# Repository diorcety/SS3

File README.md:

# SS3 — Solder Station 3

A DIY Weller-compatible soldering station controller, inspired by the [kair.us Weller WMRP and WMRT compatible soldering station](http://kair.us/projects/weller/index.html).

## Overview

SS3 is a two-board redesign of the kair.us open-source solder station. The key differences from the original are:

- **Transformer-based power supply** instead of SMPS — cleaner, simpler, lower EMI
- **Native 12V and 24V tip support** — handle type is identified by reading a resistor inside the handle via a voltage divider (510Ω for WXUP, 1kΩ for WMRP, 2kΩ for WMRT)
- **MSPM0G1507SRHBR MCU** (Texas Instruments) replacing the PIC16F1788
- **Dual MOSFET back-to-back switching stage** acting as a solid-state triac with minimal conduction losses

## Hardware — Two Boards

### MCU / Display Board
Handles all control logic, ADC measurements, and user interface.

- MSPM0G1507SRHBR microcontroller (default)
  - MSPM0G1505SRHBR can be used for 7-segment display builds
  - MSPM0G1506SRHBR can be used for TFT display builds
  - Switching variant requires updating `device_linker.cmd`
- Onboard ADC for thermocouple sensing (cold-junction compensation is handled inside the handle itself)
- Display support:
  - 4× 7-segment LED display
  - 1.9" TFT color screen

### Power Board
Drives the resistive heating element of the tip.

- Four dual N-MOSFET ICs (8 MOSFETs total), one per heating channel: two channels (left/right) × two voltages (12V/24V), each pair wired back-to-back
- Each pair acts as a solid-state triac equivalent, covering both 12V and 24V channels
- Lower switching losses compared to a traditional triac

## Tip Compatibility

Compatible with Weller active tips using an integrated heater and thermocouple:

- **WMRP** — soldering pen (12V)
- **WMRT** — desoldering tweezers (12V)
- **WXUP** — soldering pen (24V)

## Directory Structure

```
SS3/
├── 3D/       — Stands and handle models (12V and 24V variants; no enclosure provided)
├── PCBS/     — KiCad / Gerber files for both boards, plus KiCad conversions of the
│              original kair.us WMRP and WMRT boards (including mirrored variant for
│              mirrored jack barrels)
├── SIMS/     — LTSpice simulations: zero-cross detection, 3.6V SMPS from half-wave
│              rectifier, and back-to-back N-MOSFET triac equivalent
└── SS3/      — Firmware source (CMake project)
```

## Credits

Based on the open-source [Weller WMRP and WMRT compatible soldering station](http://kair.us/projects/weller/index.html) by kair.us.

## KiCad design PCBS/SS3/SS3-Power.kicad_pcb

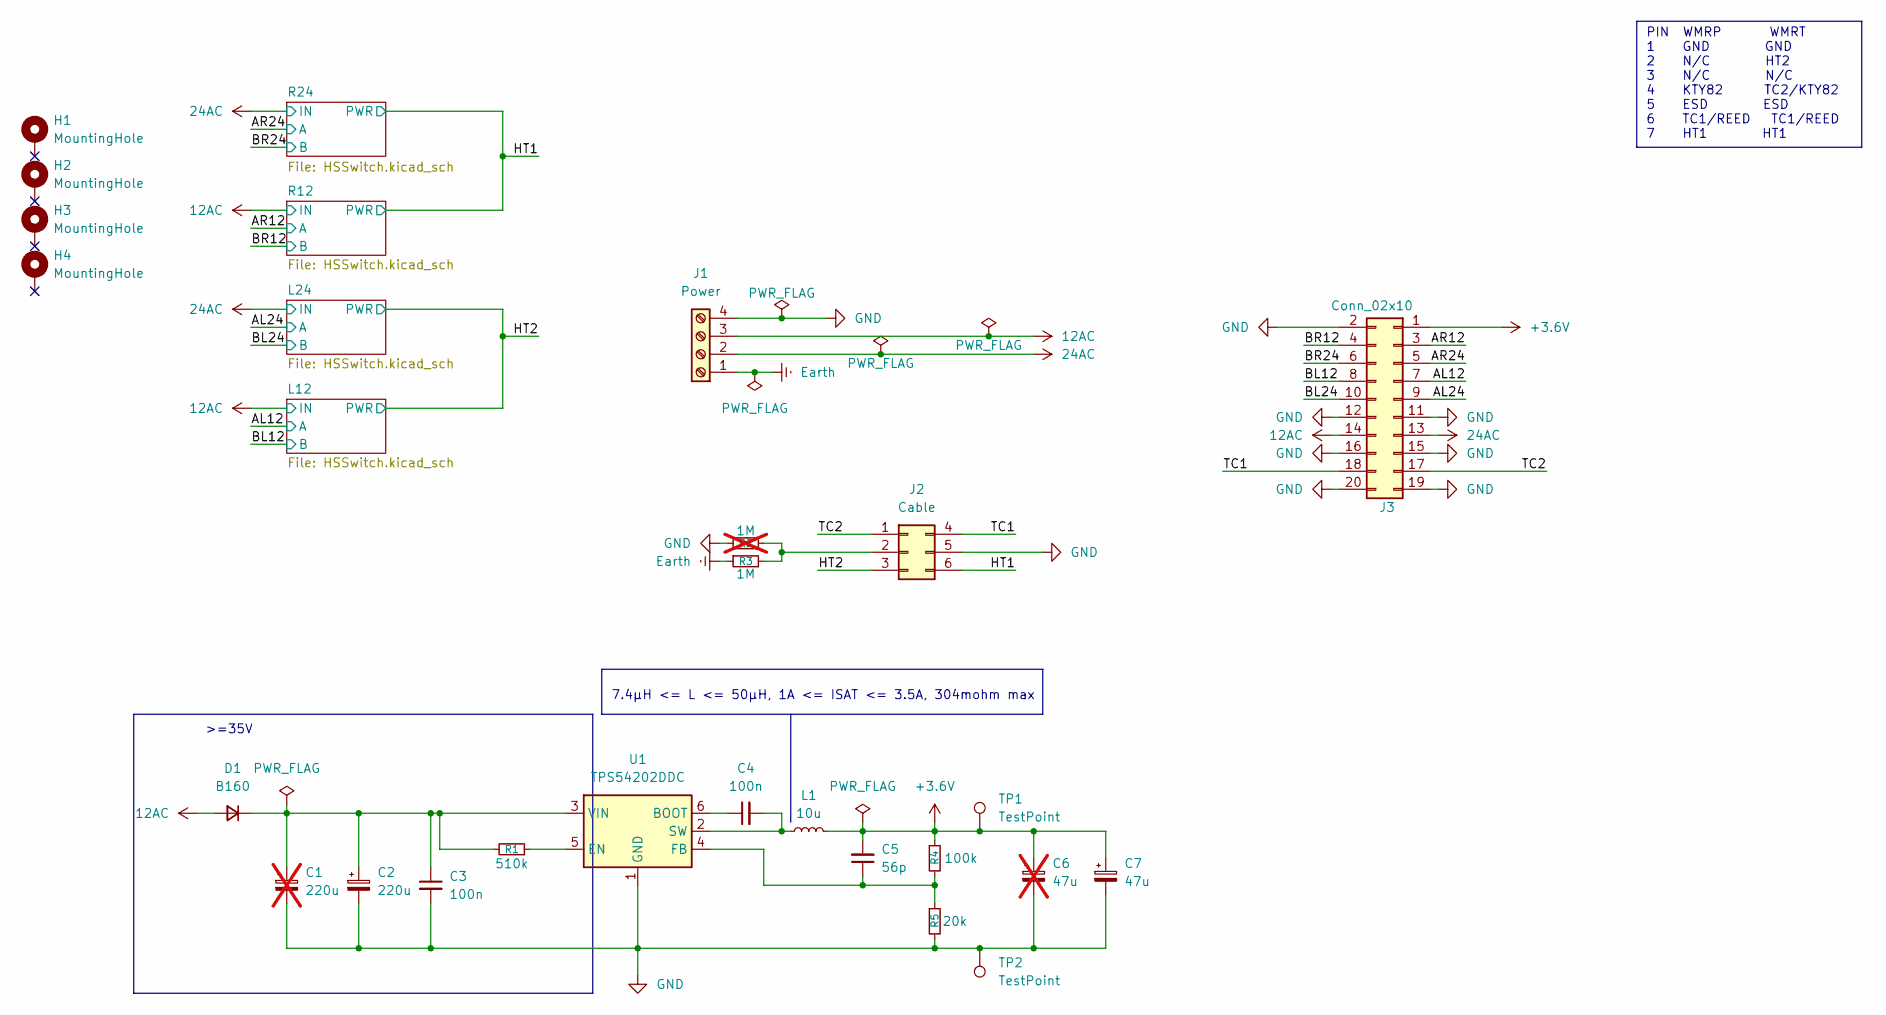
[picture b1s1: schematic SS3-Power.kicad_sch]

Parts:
C1: 220u; CP_Elec_10x10.5; not fitted
C2: 220u; CP_Elec_10x10.5
C3, C4: 100n; C_0402_1005Metric
C5: 56p; C_0402_1005Metric
C6: 47u; CP_Elec_6.3x5.9; not fitted
C7: 47u; CP_Elec_6.3x5.9
D1: B160; D_SMB
H1, H2, H3, H4: MountingHole; MountingHole_2mm_M1.8_Pad
J1: Power; TerminalBlock_Phoenix_PT-1,5-4-3.5-H_1x04_P3.50mm_Horizontal
J2: Cable; 10127720-061LF
J3: Conn_02x10; BF030-20A-B1-0360
L1: 10u; L_Chilisin_BWVS00606045
R1: 510k; R_0402_1005Metric
R2: 1M; R_0402_1005Metric; not fitted
R3: 1M; R_0402_1005Metric
R4: 100k; R_0402_1005Metric
R5: 20k; R_0402_1005Metric
TP1, TP2: TestPoint; TestPoint_THTPad_D2.0mm_Drill1.0mm
U1: TPS54202DDC; SOT-23-6

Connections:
12AC: D1.2 (A), J1.3, J3.14; also elsewhere on the board
24AC: J1.2, J3.13; also elsewhere on the board
+3.6V: C5.2, C6.1, C7.1, J3.1, L1.2, R4.1, TP1.1 (1_1)
/AL12: J3.7; also elsewhere on the board
/AL24: J3.9; also elsewhere on the board
/AR12: J3.3; also elsewhere on the board
/AR24: J3.5; also elsewhere on the board
/BL12: J3.8; also elsewhere on the board
/BL24: J3.10; also elsewhere on the board
/BR12: J3.4; also elsewhere on the board
/BR24: J3.6; also elsewhere on the board
/HT1: J2.6; also elsewhere on the board
/HT2: J2.3; also elsewhere on the board
/TC1: J2.4, J3.18
/TC2: J2.1, J3.17
Earth: J1.1, R3.1
GND: C1.2, C2.2, C3.2, C6.2, C7.2, J1.4, J2.5, J3.2, J3.11, J3.12, J3.15, J3.16, J3.19, J3.20, R2.2, R5.2, TP2.1 (1_1), U1.1 (GND); also elsewhere on the board
unnamed: C1.1, C2.1, C3.1, D1.1 (K), R1.2, U1.3 (VIN)
unnamed: J2.2, R2.1, R3.2
unnamed: C4.1, U1.6 (BOOT)
unnamed: R1.1, U1.5 (EN)
unnamed: C5.1, R4.2, R5.1, U1.4 (FB)
unnamed: C4.2, L1.1, U1.2 (SW)

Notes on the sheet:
PIN WMRP WMRT 1 GND GND 2 N/C HT2 3 N/C N/C 4 KTY82 TC2/KTY82 5 ESD ESD 6 TC1/REED TC1/REED 7 HT1 HT1
>=35V
7.4μH <= L <= 50μH, 1A <= ISAT <= 3.5A, 304mohm max

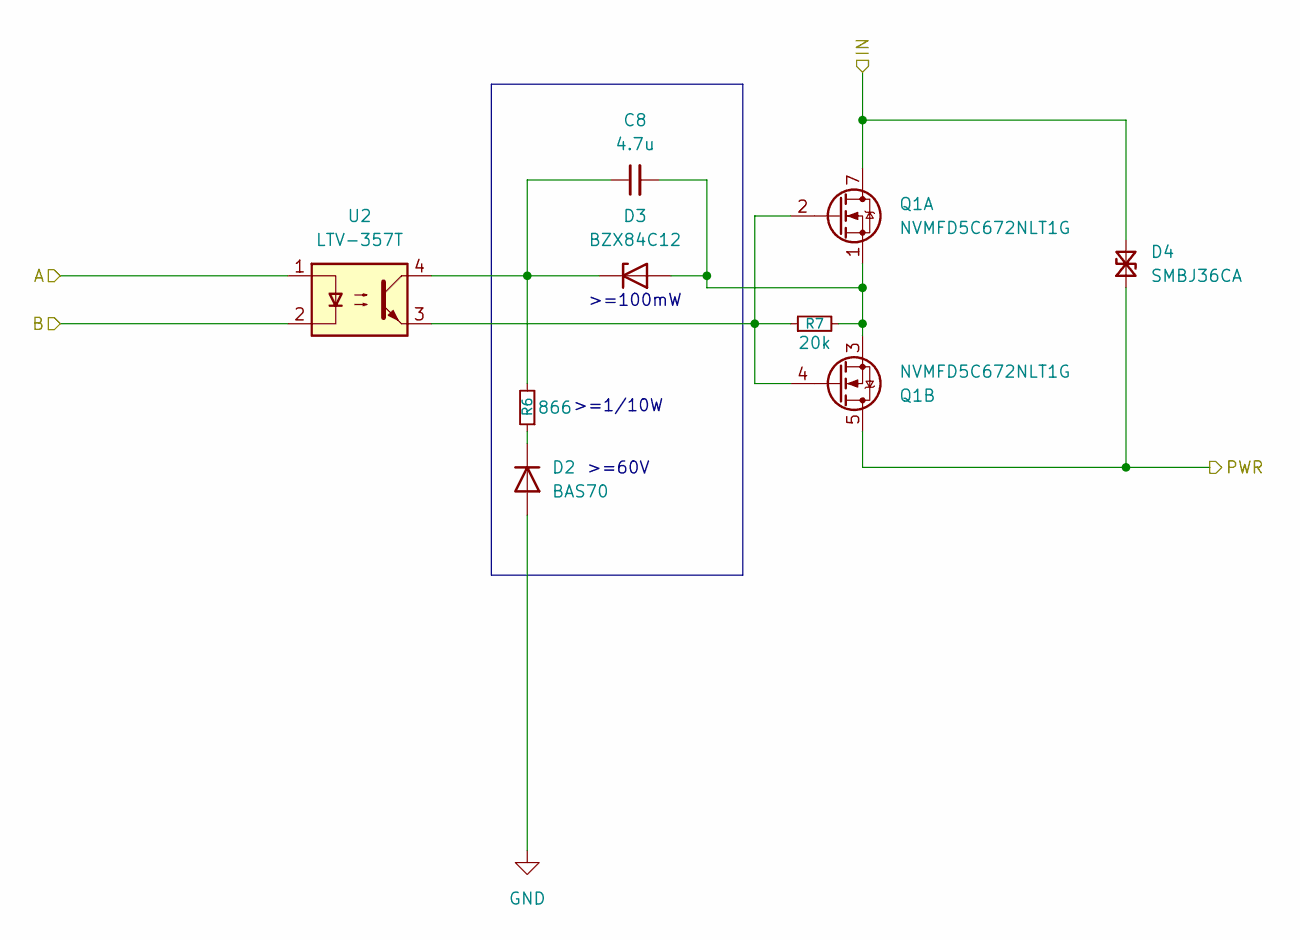
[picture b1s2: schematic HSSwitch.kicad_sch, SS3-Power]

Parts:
C8: 4.7u; C_0805_2012Metric
D2: BAS70; SOT-23
D3: BZX84C12; SOT-23
D4: SMBJ36CA; D_SMB
Q1: NVMFD5C672NLT1G; Mouser Part Number 863-NVMFD5C672NLT1G
R6: 866; R_0805_2012Metric
R7: 20k; R_0402_1005Metric
U2: LTV-357T; SO-4_4.4x3.6mm_P2.54mm

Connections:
24AC: D4.2 (A2), Q1.7, Q1.8 (D), Q1.9 (D), Q1.10 (D), Q1.11 (D); also elsewhere on the board
/AR24: U2.1; also elsewhere on the board
/BR24: U2.2; also elsewhere on the board
/HT1: D4.1 (A1), Q1.5, Q1.6 (D), Q1.12 (D), Q1.13 (D), Q1.14 (D); also elsewhere on the board
GND: D2.1 (A); also elsewhere on the board
unnamed: D2.3 (K), R6.1
unnamed: C8.2, D3.1 (A), Q1.1, Q1.3, R7.2
unnamed: C8.1, D3.3 (K), R6.2, U2.4
unnamed: Q1.2, Q1.4, R7.1, U2.3

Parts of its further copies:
C9, C10, C11: 4.7u; C_0805_2012Metric
D5, D8, D11: BAS70; SOT-23
D6, D9, D12: BZX84C12; SOT-23
D7, D10, D13: SMBJ36CA; D_SMB
Q2, Q3, Q4: NVMFD5C672NLT1G; Mouser Part Number 863-NVMFD5C672NLT1G
R8, R10, R12: 866; R_0805_2012Metric
R9, R11, R13: 20k; R_0402_1005Metric
U3, U4, U5: LTV-357T; SO-4_4.4x3.6mm_P2.54mm

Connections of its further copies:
12AC: D7.2 (A2), D13.2 (A2), Q2.7, Q2.8 (D), Q2.9 (D), Q2.10 (D), Q2.11 (D), Q4.7, Q4.8 (D), Q4.9 (D), Q4.10 (D), Q4.11 (D); also elsewhere on the board
24AC: D10.2 (A2), Q3.7, Q3.8 (D), Q3.9 (D), Q3.10 (D), Q3.11 (D); also elsewhere on the board
/AL12: U5.1; also elsewhere on the board
/AL24: U4.1; also elsewhere on the board
/AR12: U3.1; also elsewhere on the board
/BL12: U5.2; also elsewhere on the board
/BL24: U4.2; also elsewhere on the board
/BR12: U3.2; also elsewhere on the board
/HT1: D7.1 (A1), Q2.5, Q2.6 (D), Q2.12 (D), Q2.13 (D), Q2.14 (D); also elsewhere on the board
/HT2: D10.1 (A1), D13.1 (A1), Q3.5, Q3.6 (D), Q3.12 (D), Q3.13 (D), Q3.14 (D), Q4.5, Q4.6 (D), Q4.12 (D), Q4.13 (D), Q4.14 (D); also elsewhere on the board
GND: D5.1 (A), D8.1 (A), D11.1 (A); also elsewhere on the board
unnamed: D5.3 (K), R8.1
unnamed: C9.2, D6.1 (A), Q2.1, Q2.3, R9.2
unnamed: C9.1, D6.3 (K), R8.2, U3.4
unnamed: D8.3 (K), R10.1
unnamed: C10.2, D9.1 (A), Q3.1, Q3.3, R11.2
unnamed: C10.1, D9.3 (K), R10.2, U4.4
unnamed: D11.3 (K), R12.1
unnamed: C11.2, D12.1 (A), Q4.1, Q4.3, R13.2
unnamed: C11.1, D12.3 (K), R12.2, U5.4
unnamed: Q2.2, Q2.4, R9.1, U3.3
unnamed: Q3.2, Q3.4, R11.1, U4.3
unnamed: Q4.2, Q4.4, R13.1, U5.3

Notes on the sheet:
>=100mW
>=60V
>=1/10W

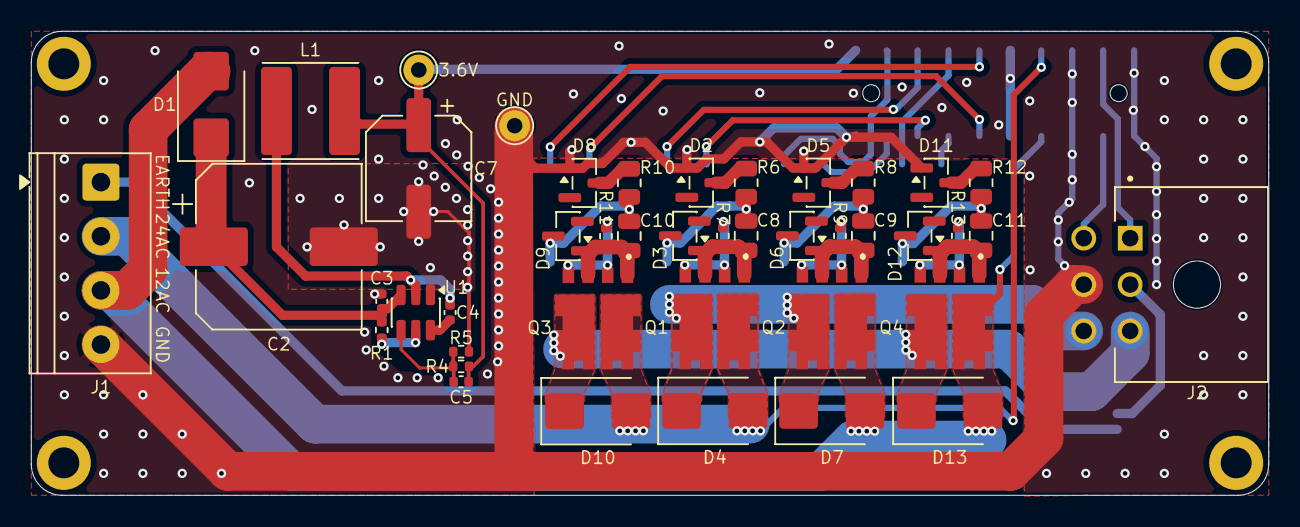
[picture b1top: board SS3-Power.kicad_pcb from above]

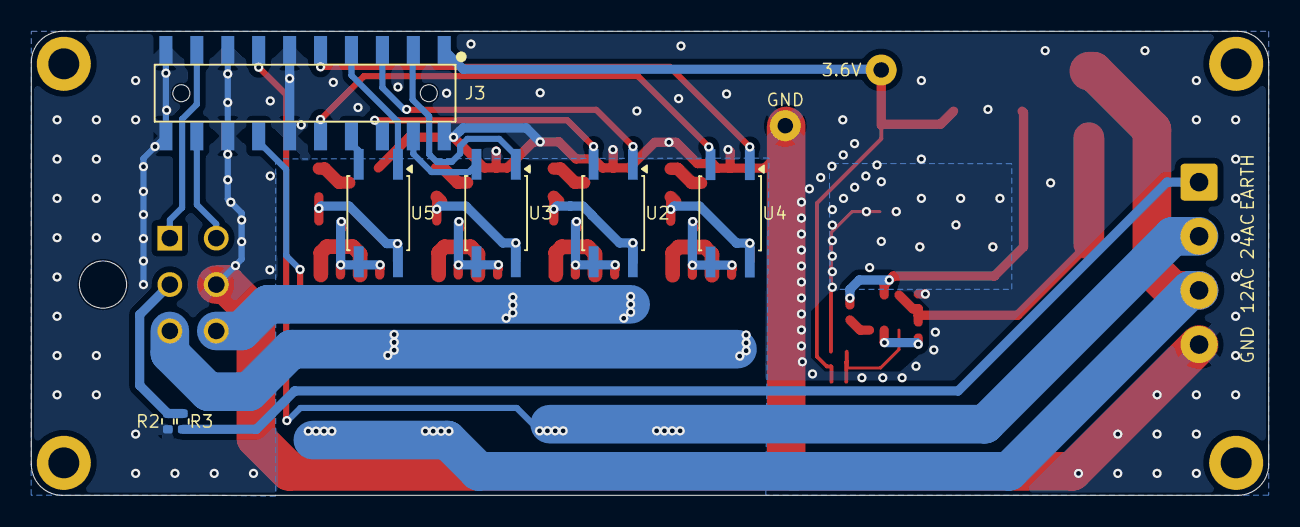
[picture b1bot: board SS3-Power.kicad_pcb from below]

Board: 2 copper layers, 80.0 x 30.0 mm, 54 parts (7 on the bottom side), 39 nets.

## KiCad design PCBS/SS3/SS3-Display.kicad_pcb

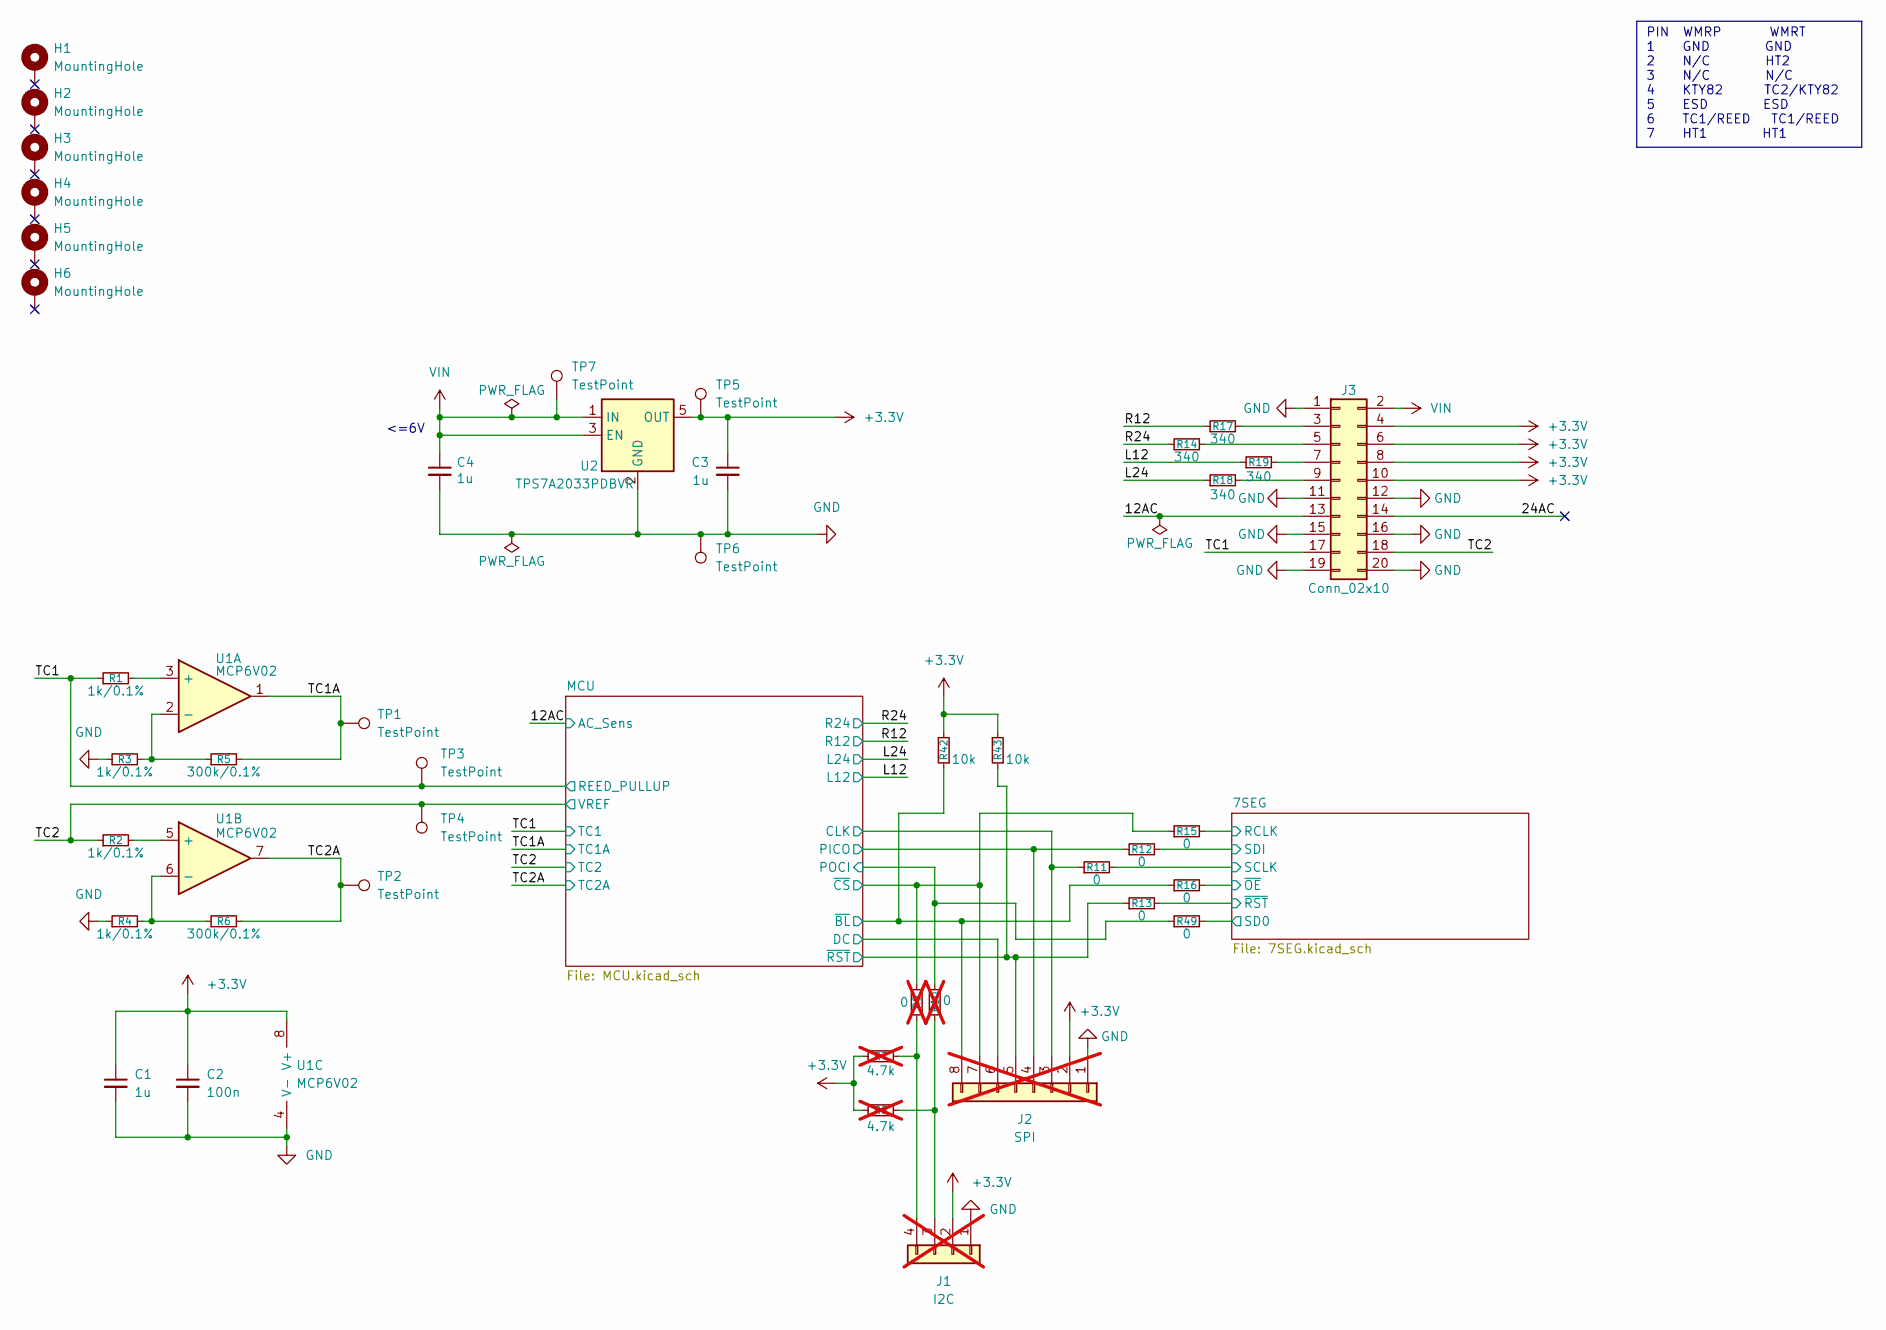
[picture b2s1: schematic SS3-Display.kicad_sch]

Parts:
C1, C3, C4: 1u; C_0402_1005Metric
C2: 100n; C_0402_1005Metric
H1, H2, H3, H4, H5, H6: MountingHole; MountingHole_2mm_M1.8_Pad
J1: I2C; PinHeader_1x04_P2.54mm_Vertical; not fitted
J2: SPI; PinHeader_1x08_P2.54mm_Vertical; not fitted
J3: Conn_02x10; BF100-20-A-D-1-0640
R1, R2, R3, R4: 1k/0.1%; R_0402_1005Metric
R5, R6: 300k/0.1%; R_0402_1005Metric
R7, R8: 4.7k; R_0402_1005Metric; not fitted
R9, R10: 0; R_0402_1005Metric; not fitted
R11, R12, R13, R15, R16, R49: 0; R_0402_1005Metric
R14, R17, R18, R19: 340; R_0402_1005Metric
R42, R43: 10k; R_0402_1005Metric
TP1, TP2, TP3, TP4, TP5, TP6, TP7: TestPoint; TestPoint_THTPad_D2.0mm_Drill1.0mm
U1: MCP6V02; SOIC-8_3.9x4.9mm_P1.27mm
U2: TPS7A2033PDBVR; SOT-23-5

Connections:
+3.3V: C1.1, C2.1, C3.1, J1.2, J2.2, J3.4, J3.6, J3.8, J3.10, R7.2, R8.2, R42.2, R43.2, TP5.1 (1_1), U1.8 (V+), U2.5 (OUT); also elsewhere on the board
/7SEG/RCLK: R15.2; also elsewhere on the board
/7SEG/SCLK: R11.2; also elsewhere on the board
/7SEG/SD0: R49.2; also elsewhere on the board
/7SEG/SDI: R12.2; also elsewhere on the board
/7SEG/~OE: R16.2; also elsewhere on the board
/7SEG/~RST: R13.2; also elsewhere on the board
/12AC: J3.13; also elsewhere on the board
/24AC: J3.14
/L12: R19.1; also elsewhere on the board
/L24: R18.1; also elsewhere on the board
/MCU/CLK: J2.3, R11.1; also elsewhere on the board
/MCU/DC: J2.6; also elsewhere on the board
/MCU/PICO: J2.4, R12.1; also elsewhere on the board
/MCU/POCI: R10.1, R49.1; also elsewhere on the board
/MCU/~BL: J2.8, R16.1, R42.1; also elsewhere on the board
/MCU/~CS: J2.7, R9.1, R15.1; also elsewhere on the board
/MCU/~RST: J2.5, R13.1, R43.1; also elsewhere on the board
/R12: R17.1; also elsewhere on the board
/R24: R14.1; also elsewhere on the board
/TC1: J3.17, R1.1, TP3.1 (1_1); also elsewhere on the board
/TC1A: R5.2, TP1.1 (1_1), U1.1; also elsewhere on the board
/TC2: J3.18, R2.1, TP4.1 (1_1); also elsewhere on the board
/TC2A: R6.2, TP2.1 (1_1), U1.7; also elsewhere on the board
GND: C1.2, C2.2, C3.2, C4.2, J1.1, J2.1, J3.1, J3.11, J3.12, J3.15, J3.16, J3.19, J3.20, R3.1, R4.1, TP6.1 (1_1), U1.4 (V-), U2.2 (GND); also elsewhere on the board
unnamed: J1.3, R8.1, R10.2
unnamed: J1.4, R7.1, R9.2
unnamed: J3.3, R17.2
unnamed: J3.5, R14.2
unnamed: J3.7, R19.2
unnamed: J3.9, R18.2
unnamed: R1.2, U1.3 (+)
unnamed: R3.2, R5.1, U1.2 (-)
unnamed: R2.2, U1.5 (+)
unnamed: R4.2, R6.1, U1.6 (-)
VIN: C4.1, J3.2, TP7.1 (1_1), U2.1 (IN), U2.3 (EN)

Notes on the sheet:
<=6V
PIN WMRP WMRT 1 GND GND 2 N/C HT2 3 N/C N/C 4 KTY82 TC2/KTY82 5 ESD ESD 6 TC1/REED TC1/REED 7 HT1 HT1

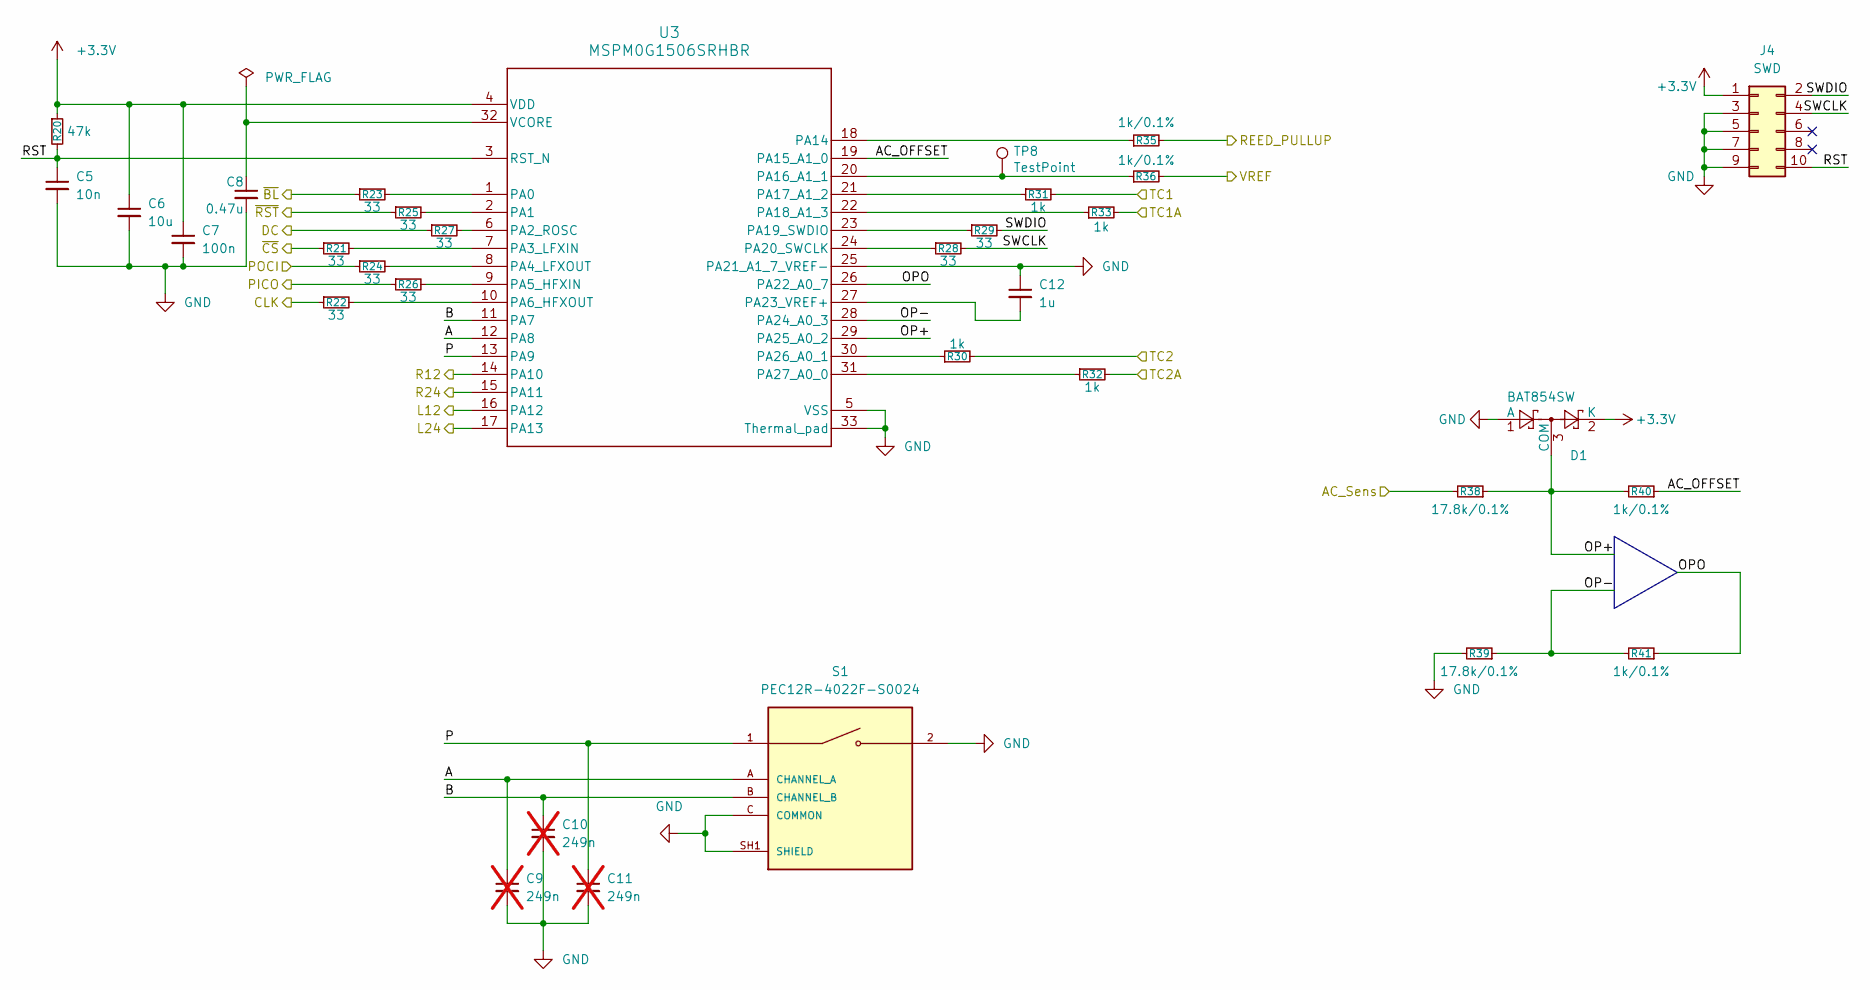
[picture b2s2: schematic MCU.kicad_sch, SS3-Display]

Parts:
C5: 10n; C_0402_1005Metric
C6: 10u; C_0603_1608Metric
C7: 100n; C_0402_1005Metric
C8: 0.47u; C_0402_1005Metric
C9, C10, C11: 249n; C_0402_1005Metric; not fitted
C12: 1u; C_0402_1005Metric
D1: BAT854SW; SOT-323_SC-70
J4: SWD; 20021511-00010T4LF
R20: 47k; R_0402_1005Metric
R21, R22, R23, R24, R25, R26, R27, R28, R29: 33; R_0402_1005Metric
R30, R31, R32, R33: 1k; R_0402_1005Metric
R35, R36, R40, R41: 1k/0.1%; R_0402_1005Metric
R38, R39: 17.8k/0.1%; R_0402_1005Metric
S1: PEC12R-4022F-S0024; PARTREV 07/21; DigiKey_Part_Number PEC12R-4022F-S0024-ND
TP8: TestPoint; TestPoint_THTPad_D2.0mm_Drill1.0mm
U3: MSPM0G1506SRHBR; VQFN-32-1EP_5x5mm_P0.5mm_EP3.5x3.5mm_ThermalVias

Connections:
+3.3V: C6.1, C7.1, D1.2 (K), J4.1, R20.1, U3.4 (VDD); also elsewhere on the board
/12AC: R38.2; also elsewhere on the board
/L12: U3.16 (PA12); also elsewhere on the board
/L24: U3.17 (PA13); also elsewhere on the board
/MCU/A: C9.1, S1.A (CHANNEL_A), U3.12 (PA8)
/MCU/AC_OFFSET: R40.1, U3.19 (PA15_A1_0)
/MCU/B: C10.1, S1.B (CHANNEL_B), U3.11 (PA7)
/MCU/CLK: R22.1; also elsewhere on the board
/MCU/DC: R27.1; also elsewhere on the board
/MCU/OP+: D1.3 (COM), R38.1, R40.2, U3.29 (PA25_A0_2)
/MCU/OP-: R39.1, R41.2, U3.28 (PA24_A0_3)
/MCU/OPO: R41.1, U3.26 (PA22_A0_7)
/MCU/P: C11.1, S1.1, U3.13 (PA9)
/MCU/PICO: R26.1; also elsewhere on the board
/MCU/POCI: R24.1; also elsewhere on the board
/MCU/RST: C5.1, J4.10, R20.2, U3.3 (RST_N)
/MCU/SWCLK: J4.4, R28.2
/MCU/SWDIO: J4.2, R29.2
/MCU/~BL: R23.1; also elsewhere on the board
/MCU/~CS: R21.1; also elsewhere on the board
/MCU/~RST: R25.1; also elsewhere on the board
/R12: U3.14 (PA10); also elsewhere on the board
/R24: U3.15 (PA11); also elsewhere on the board
/TC1: R31.2, R35.2; also elsewhere on the board
/TC1A: R33.2; also elsewhere on the board
/TC2: R30.2, R36.2; also elsewhere on the board
/TC2A: R32.2; also elsewhere on the board
GND: C5.2, C6.2, C7.2, C8.2, C9.2, C10.2, C11.2, C12.1, D1.1 (A), J4.3, J4.5, J4.7, J4.9, R39.2, S1.2, S1.C (COMMON), S1.SH1 (SHIELD), S1.SH2 (SHIELD), U3.5 (VSS), U3.25 (PA21_A1_7_VREF-), U3.33 (Thermal_pad); also elsewhere on the board
unnamed: R23.2, U3.1 (PA0)
unnamed: R25.2, U3.2 (PA1)
unnamed: R27.2, U3.6 (PA2_ROSC)
unnamed: R21.2, U3.7 (PA3_LFXIN)
unnamed: R24.2, U3.8 (PA4_LFXOUT)
unnamed: R26.2, U3.9 (PA5_HFXIN)
unnamed: R22.2, U3.10 (PA6_HFXOUT)
unnamed: R35.1, U3.18 (PA14)
unnamed: R36.1, TP8.1 (1_1), U3.20 (PA16_A1_1)
unnamed: R31.1, U3.21 (PA17_A1_2)
unnamed: R33.1, U3.22 (PA18_A1_3)
unnamed: R29.1, U3.23 (PA19_SWDIO)
unnamed: R28.1, U3.24 (PA20_SWCLK)
unnamed: C12.2, U3.27 (PA23_VREF+)
unnamed: R30.1, U3.30 (PA26_A0_1)
unnamed: R32.1, U3.31 (PA27_A0_0)
unnamed: C8.1, U3.32 (VCORE)

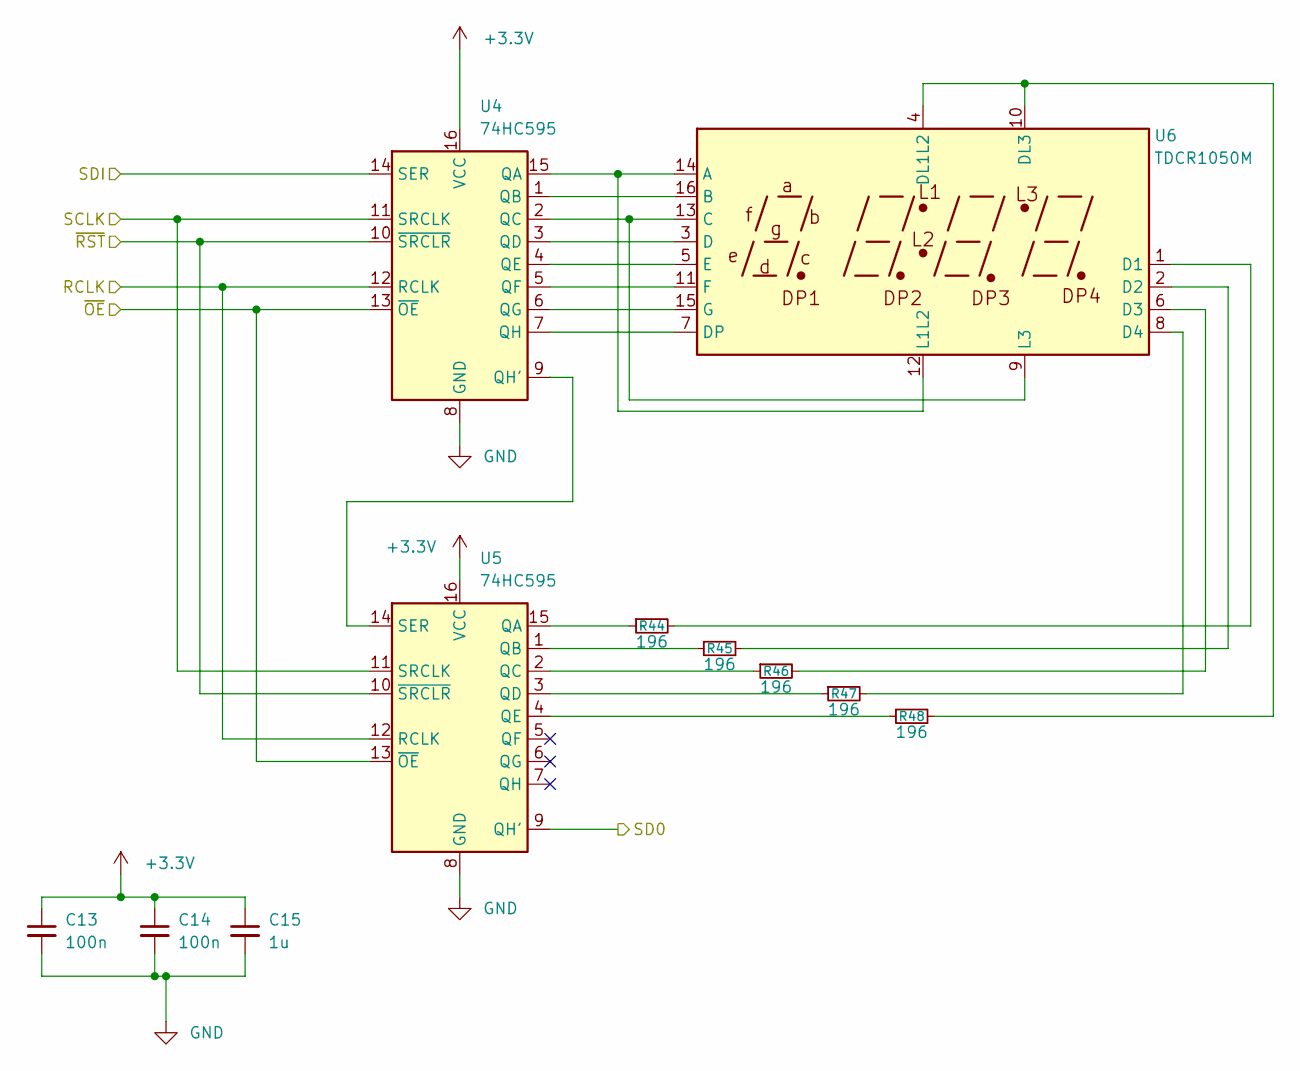
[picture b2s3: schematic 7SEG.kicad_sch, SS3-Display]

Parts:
C13, C14: 100n; C_0402_1005Metric
C15: 1u; C_0402_1005Metric
R44, R45, R46, R47, R48: 196; R_0402_1005Metric
U4, U5: 74HC595; TSSOP-16_4.4x5mm_P0.65mm
U6: TDCR1050M

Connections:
+3.3V: C13.1, C14.1, C15.1, U4.16 (VCC), U5.16 (VCC); also elsewhere on the board
/7SEG/RCLK: U4.12 (RCLK), U5.12 (RCLK); also elsewhere on the board
/7SEG/SCLK: U4.11 (SRCLK), U5.11 (SRCLK); also elsewhere on the board
/7SEG/SD0: U5.9 (QH'); also elsewhere on the board
/7SEG/SDI: U4.14 (SER); also elsewhere on the board
/7SEG/~OE: U4.13 (~OE), U5.13 (~OE); also elsewhere on the board
/7SEG/~RST: U4.10 (~SRCLR), U5.10 (~SRCLR); also elsewhere on the board
GND: C13.2, C14.2, C15.2, U4.8 (GND), U5.8 (GND); also elsewhere on the board
unnamed: U4.15 (QA), U6.12 (L1L2), U6.14 (A)
unnamed: U4.1 (QB), U6.16 (B)
unnamed: U4.2 (QC), U6.9 (L3), U6.13 (C)
unnamed: U4.3 (QD), U6.3 (D)
unnamed: U4.4 (QE), U6.5 (E)
unnamed: U4.5 (QF), U6.11 (F)
unnamed: U4.6 (QG), U6.15 (G)
unnamed: U4.9 (QH'), U5.14 (SER)
unnamed: U4.7 (QH), U6.7 (DP)
unnamed: R44.1, U5.15 (QA)
unnamed: R45.1, U5.1 (QB)
unnamed: R46.1, U5.2 (QC)
unnamed: R47.1, U5.3 (QD)
unnamed: R48.1, U5.4 (QE)
unnamed: R44.2, U6.1 (D1)
unnamed: R45.2, U6.2 (D2)
unnamed: R46.2, U6.6 (D3)
unnamed: R47.2, U6.8 (D4)
unnamed: R48.2, U6.4 (DL1L2), U6.10 (DL3)

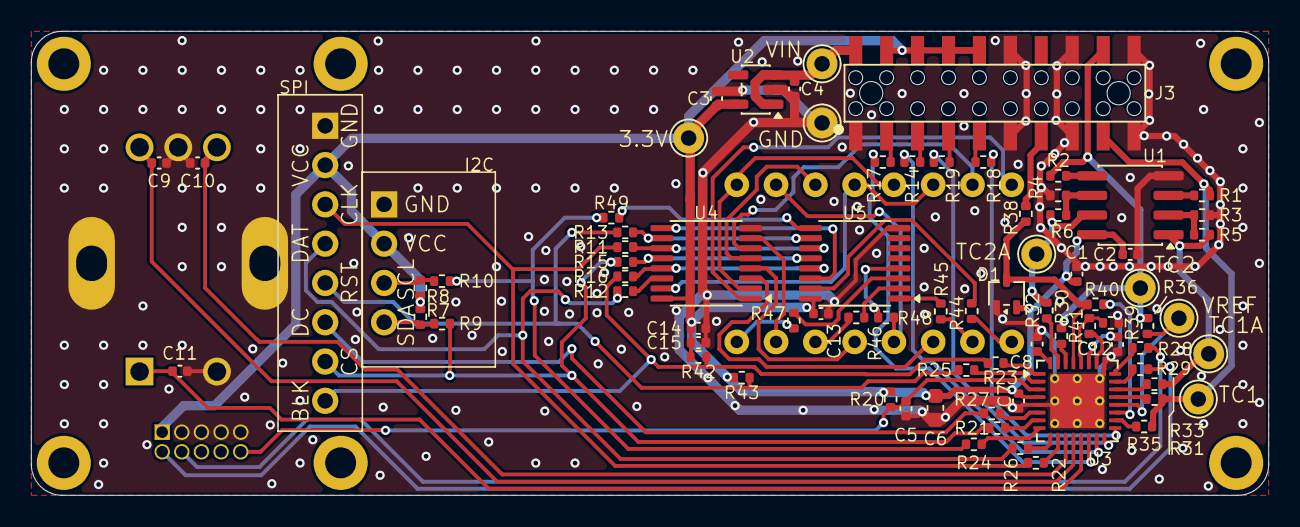
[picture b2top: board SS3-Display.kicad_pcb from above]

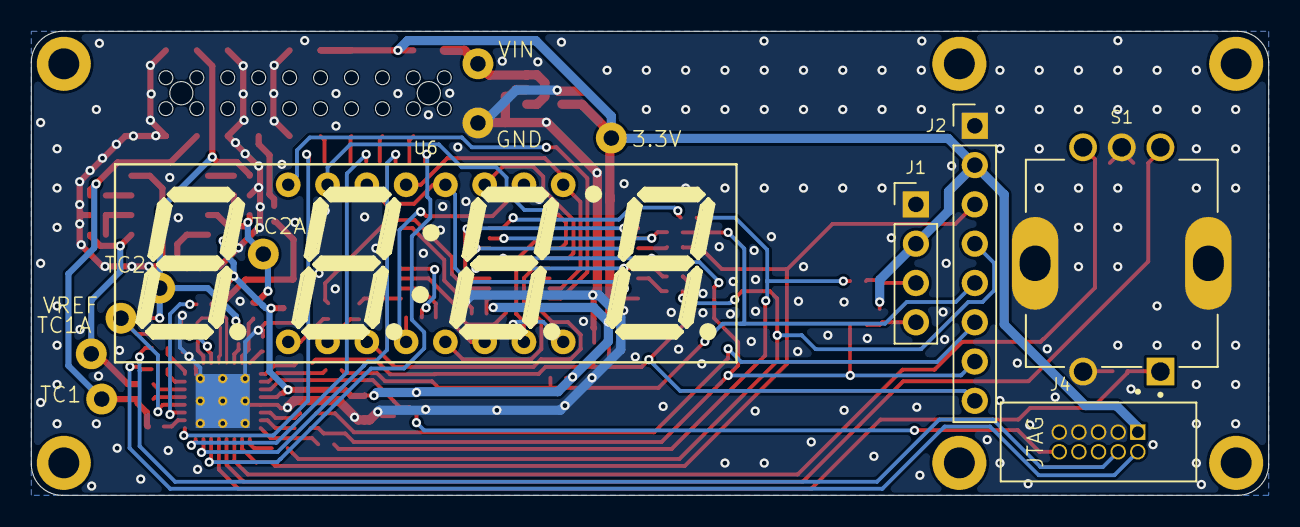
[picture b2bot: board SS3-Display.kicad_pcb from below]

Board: 2 copper layers, 80.0 x 30.0 mm, 88 parts (5 on the bottom side), 81 nets.

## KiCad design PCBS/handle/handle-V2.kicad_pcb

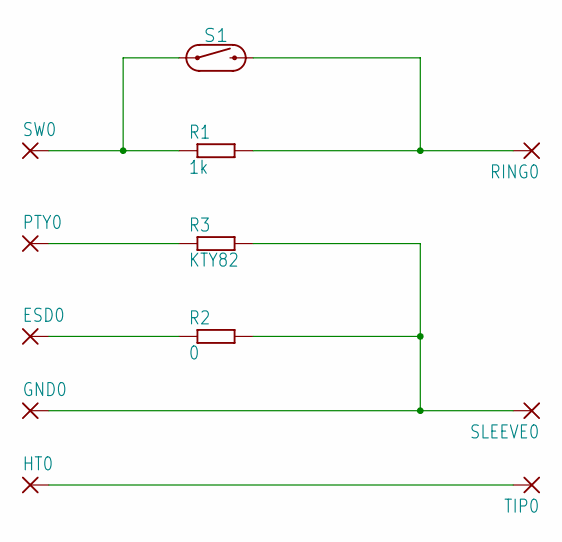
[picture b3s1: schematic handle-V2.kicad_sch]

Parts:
ESD0: SMD2; SMD1,27-2,54
GND0: WIREPADSMD5-1,8; 5-1,8
HT0: WIREPADSMD5-1,8; 5-1,8
PTY0: SMD2; SMD1,27-2,54
R1: 1k; R0805
R2: 0; R0805
R3: KTY82; R0805
RING0: WIREPADSMD5-1,8; 5-1,8
S1: REED_SWITCH-PTH-INSULATED; REED_SWITCH_PLASTIC
SLEEVE0: WIREPADSMD5-1,8; 5-1,8
SW0: SMD2; SMD1,27-2,54
TIP0: WIREPADSMD5-1,8; 5-1,8

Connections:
ESD: ESD0.1, R2.1
GND: GND0.1, R2.2, R3.2, SLEEVE0.1
HEATHER: HT0.1, TIP0.1
unnamed: R1.2, RING0.1, S1.P$2 (2)
PTC: PTY0.1, R3.1
SW: R1.1, S1.P$1 (1), SW0.1

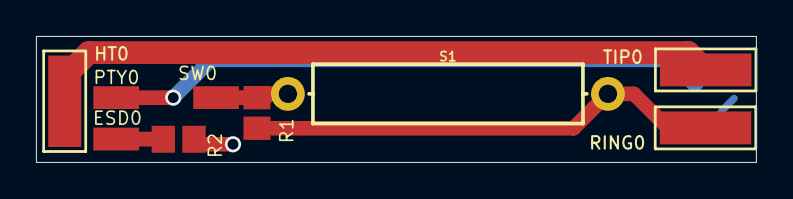
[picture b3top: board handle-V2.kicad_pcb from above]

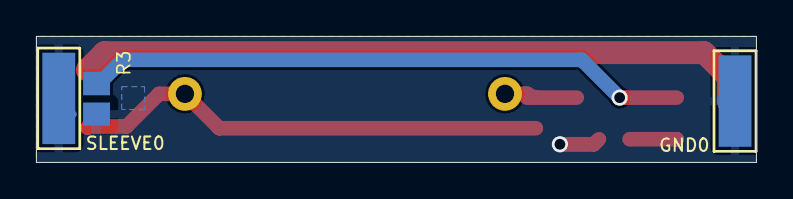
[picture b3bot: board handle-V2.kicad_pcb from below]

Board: 2 copper layers, 40.0 x 7.0 mm, 12 parts (3 on the bottom side), 6 nets.

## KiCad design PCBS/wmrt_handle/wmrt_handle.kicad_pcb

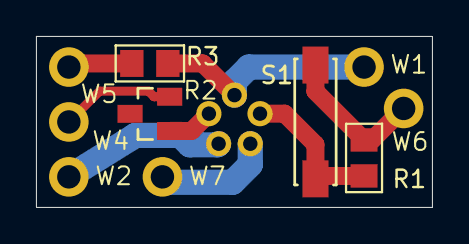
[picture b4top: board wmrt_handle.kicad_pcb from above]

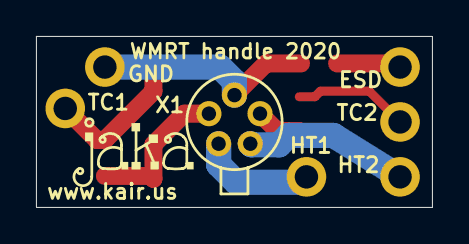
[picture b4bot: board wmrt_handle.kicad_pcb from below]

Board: 2 copper layers, 22.0 x 9.5 mm, 12 parts (2 on the bottom side), 8 nets.

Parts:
R1: 2k; R0805
R2: KTY82/110; SOT-23
R3: 0R; R0805
S1: RI80SMDM-0510-J1; RI-80_SMDM_J-1
U$1: JAKA_LOGO_SILK_NANO; JAKA_SILK_NANO
W1, W2, W4, W5, W6, W7: TESTPOINTTH_1MM3_ROUND; P1-13-R
X1: 09-9792-20-05; 09-9792-20-05_BINDER

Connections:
GND: R3.1, W1.TP, X1.3
unnamed: R2.2, W4.TP
unnamed: R2.1, X1.4
unnamed: R1.2, S1.2, W6.TP
unnamed: R1.1, S1.1, X1.2
unnamed: W2.TP, X1.5
unnamed: W7.TP, X1.1
unnamed: R3.2, W5.TP

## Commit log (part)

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2026-04-27 Add CMake project
2026-04-27 Remove CCS files
2026-04-29 Add MATHACL module
2026-04-29 Fix ZCD
2026-04-29 Fix Switch namings
2026-04-29 Iron: use correct temperature for left_duty
2026-04-29 Set correct values for default setback/idle duty
2026-04-29 seg7: Improve display_number function
2026-04-29 seg7: Display the correct setpoint(heat_setpoint) when this one is changed
2026-04-29 seg7: Improve display by using colon for non normal state, left-most dot for left duty and central dot for reed state
2026-04-29 iron: enable output
2026-04-30 Acquisition: increase median filter size
2026-04-30 seg7: avoid flickering of the temperature around a value
2026-05-08 Add fail-safe protection for misconnected tip
    Add a third measurement of the raw voltage on the TC pin and immediately
    shut down power if it exceeds a safety threshold, then enter the error state.
2026-05-08 Iron: filter setpoint to avoid heat spikes at startup
2026-05-08 Eeprom: enabled
2026-05-08 seg7: reduce IIR window
2026-05-08 seg7: Display setpoint changes over NC
2026-05-08 eeprom: disabled in debug
2026-05-08 Release: add NONMAIN memory
2026-05-08 seg7: don't use temperature if the tip don't have the TC
2026-05-08 seg7: use raw TC temperature in diag menu
2026-05-08 seg7: fix 0 temp display
2026-05-08 heat: don't change state without tip
2026-05-08 heat: don't change state when changing tip
2026-05-08 heat: allow to toggle from setback to normal
2026-05-08 iron: Improve error condition
2026-05-08 KTY: Use the temperature when there is not tip, and use fallback value in poor mode
2026-05-08 seg7: Use only 2 last character of the tip name Restore real WXUP name in the code Don't use anymore W or M character: doesn't display correctly
2026-05-08 seg7: keep data refresh slow in order to be readable
2026-05-08 seg7: SEG7 constant missing prefixes
2026-05-10 Replace GPIOA with the associated pin PORT
2026-05-10 calibration: add missing static const for kty_adc_table
2026-05-19 st7789: Add skeleton
2026-05-19 st7789: Working screen without DMA
2026-05-19 st7789: Working DMA by directly using parity checked SRAM and not the aliased one
2026-05-19 Remove stdlib.h usage
2026-05-19 st7789: Split c/c++ code, add custom font
2026-05-19 timer: add tick_ prefix
2026-05-19 st7789: Working DMA but using un-checked SRAM
2026-05-19 Add way to run program on computer: -DSIMULATION
2026-05-19 Arduino_GFX: Add build flags to strip unused code
2026-05-19 st7789: Update font
2026-05-19 st7789: Add missing screens
2026-05-19 Clock: Use PLL and 64Mhz MCLK
2026-05-19 st7789: Improve the screen and fix view display
2026-05-19 st7789: Align and increase stack
2026-05-19 Remove usage of snprintf
2026-05-19 Add unit tests when using -DSIMULATION
2026-05-19 st7789: Use cached value with debounce. Remove font 160. Use font 80 with x2. Use Monospace font enconding.
2026-05-19 seg7: Don't display offset in unit menu with degree fahrenheit unit
2026-05-19 iron: Move fail-safe first
2026-05-19 iron: Don't heat in standby or error state
2026-05-19 st7789/seg7: Factorize code into display
2026-06-02 st7789/seg7: Fix race condition with CACHED_VALUE_GET and ACK: use new CACHED_VALUE_GET_ACK function
2026-06-02 systick: Use a timer based on SYSOSC and MFCLK
    Using cortex systick seems really incorrect when PLL is enabled
2026-06-02 cached_value: Fix _cached_value_set logic
2026-06-02 iron: increase heat factor and update idle duty default value accordingly
    Fix also left/right heat value
2026-06-06 typo: filtred to filtered
2026-06-07 tip: debounce tip_type and reed_state. Avoiding transient value and misdetection of the tip_type during reed closing
2026-06-25 seg7: Fix display after setpoint changes
2026-06-25 Add README.md
2026-06-25 Add Simlations, 3D and PCBs
2026-06-25 Remove unused dependencies
